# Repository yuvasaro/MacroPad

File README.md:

# MacroPad Project
UCSD HKN Project Team 2024-2025

The MacroPad project is a physical macro keyboard that interacts with a companion desktop app, allowing users to trigger customized hotkeys and launch executables across different applications. From designing the PCB and firmware to building the cross-platform desktop interface, we constructed both the hardware and software aspects of this project end-to-end.

[MacroPad Project Documentation.pdf](https://github.com/user-attachments/files/27936859/MacroPad.Project.Documentation.pdf)

## System Overview
On the physical aspect, the MacroPad is a palm-sized mechanical keyboard built around an ESP32 module, featuring 9 hot-swappable keys, 2 rotary encoders, and a small OLED screen on each key that displays context-aware icons. The board connects to a desktop app over USB, sending key and encoder events while receiving profile-switch commands in return.

The desktop app runs as a background system-tray agent on Windows and macOS, automatically detecting the active application and switching between six user-configurable profiles in real time. Each profile holds 9 macros — either keystroke combinations or executable launches — and is saved locally to the OS config directory. A QML-based GUI lets users drag-and-drop icons onto keys, configure macros, and preview what will appear on each OLED display.

## Project Structure
Unlike typical macro pads that require manual profile switching, MacroPad automatically detects the active application on your computer and switches to the matching profile in real time. 

- **Macro class:** contains information about the type and content of each key.   
- **Profile class:** contains 9 macro keys.   
   - We can set up multiple profiles. profile objects are saved to the cross-platform config directory, making the app a background agent.     
   - Similar to how Logitech G Hub keeps running after the window is closed
- **UI:** A basic UI featuring the 9 key-grid for the general profile and 6 other profiles. 
   - Each key opens a configuration page where users can assign keystroke combination or an executable path which are saved to a file.
- **Hotkey Registering:** We can enter the key type and content as parameters, so it will be registering the information into a macro key in the current profile we are on.
- **Hotkey Triggering:** Everytime a hotkey is pressed, the registered executable or keystrokes will be triggered. We worked on translates a string into a list of keys that the computer can interpret. 
## Dependencies
Mac OS  
Windows 10

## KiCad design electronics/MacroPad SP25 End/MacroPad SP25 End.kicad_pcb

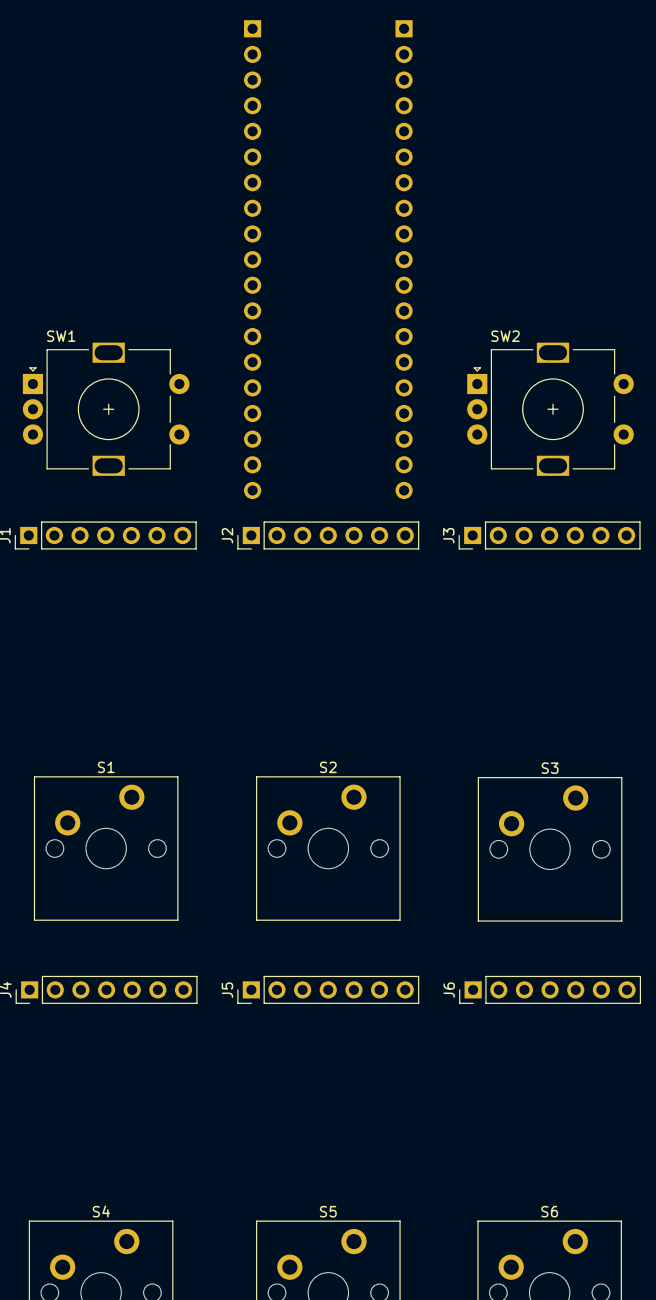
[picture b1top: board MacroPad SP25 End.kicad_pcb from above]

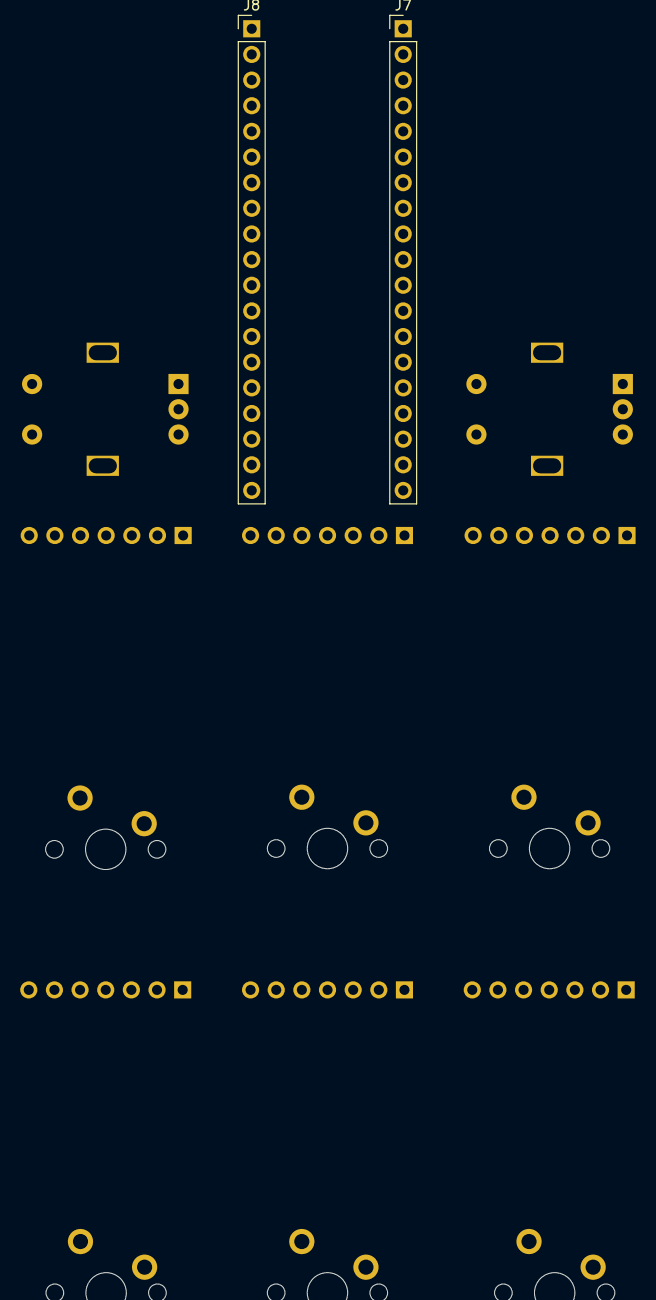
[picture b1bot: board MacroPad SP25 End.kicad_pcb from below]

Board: 2 copper layers, 16 parts (2 on the bottom side), 24 nets, no tracks yet.

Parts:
J1, J2, J3, J4, J5, J6: Conn_01x07_Pin; PinHeader_1x07_P2.54mm_Vertical
J7, J8: Conn_01x19_MountingPin; PinHeader_1x19_P2.54mm_Vertical
S1, S2, S3, S4, S5, S6: Keyswitch; MX_PCB_1.00u
SW1, SW2: RotaryEncoder_Switch; RotaryEncoder_Alps_EC11E-Switch_Vertical_H20mm

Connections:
CS1: J1.7, J8.4
CS2: J2.7, J8.10
CS3: J3.7, J7.13
CS4: J4.7, J7.12
CS5: J5.7, J7.9
CS6: J6.7, J7.8
DC: J1.6, J2.6, J3.6, J4.6, J5.6, J6.6, J8.5
Down1: J8.17, SW1.B
Down2: J8.8, SW2.B
GND: J1.1, J2.1, J3.1, J4.1, J5.1, J6.1, J8.19, S1.2, S2.2, S3.2, S4.2, S5.2, S6.2, SW1.C, SW1.S1, SW2.C, SW2.S1
Key1: J7.7, S1.1
Key2: J8.12, S2.1
Key3: J7.14, S3.1
Key4: J7.17, S4.1
Key5: J7.16, S5.1
Key6: J7.15, S6.1
Push1: J8.14, SW1.S2
Push2: J7.10, SW2.S2
RES: J1.5, J2.5, J3.5, J4.5, J5.5, J6.5, J8.7
SCL: J1.3, J2.3, J3.3, J4.3, J5.3, J6.3, J8.11
SDA: J1.4, J2.4, J3.4, J4.4, J5.4, J6.4, J8.18
Up1: J8.9, SW1.A
Up2: J7.11, SW2.A
VCC: J1.2, J2.2, J3.2, J4.2, J5.2, J6.2, J7.19

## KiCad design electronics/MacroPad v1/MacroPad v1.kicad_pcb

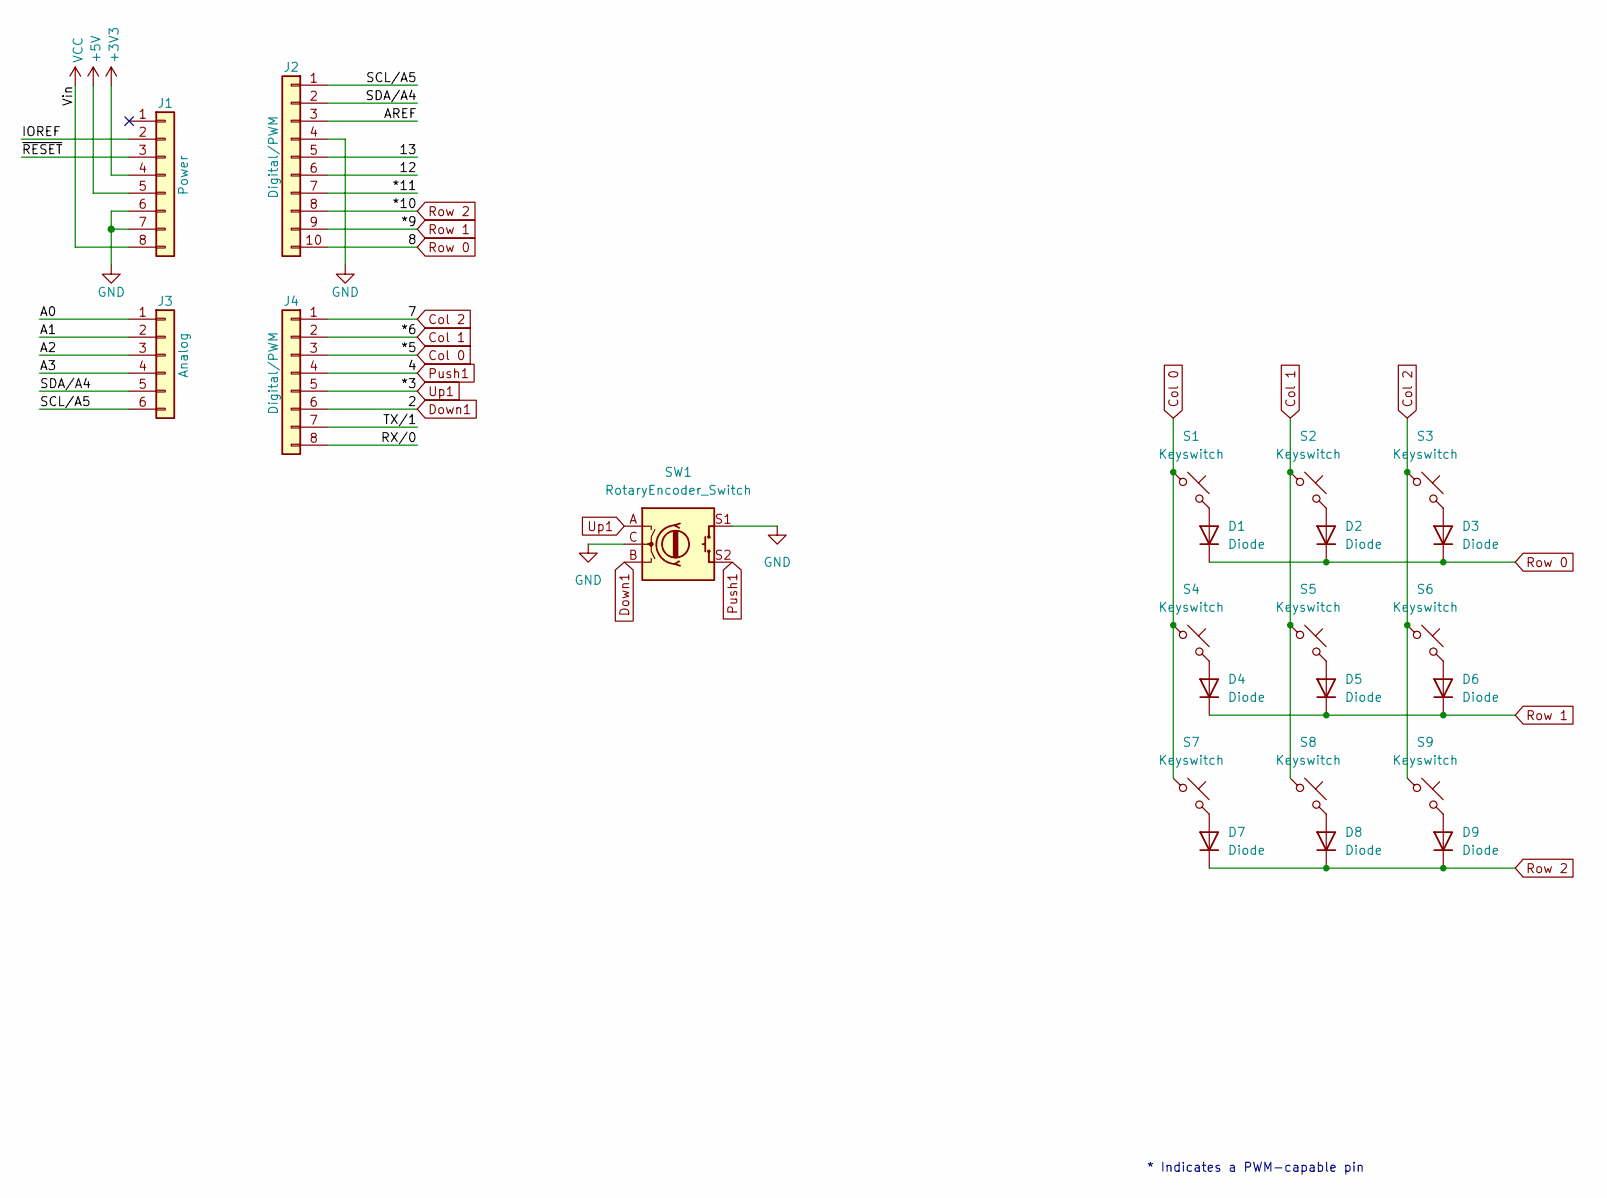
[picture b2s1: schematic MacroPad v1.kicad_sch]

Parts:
D1, D2, D3, D4, D5, D6, D7, D8, D9: Diode; Diode_DO-35
J1: Power; PinSocket_1x08_P2.54mm_Vertical
J2: Digital/PWM; PinSocket_1x10_P2.54mm_Vertical
J3: Analog; PinSocket_1x06_P2.54mm_Vertical
J4: Digital/PWM; PinSocket_1x08_P2.54mm_Vertical
S1, S2, S3, S4, S5, S6, S7, S8, S9: Keyswitch; MX_PCB_1.00u
SW1: RotaryEncoder_Switch; RotaryEncoder_Alps_EC11E-Switch_Vertical_H20mm

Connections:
+3V3: J1.4
+5V: J1.5
/12: J2.6
/13: J2.5
/*11: J2.7
/A0: J3.1
/A1: J3.2
/A2: J3.3
/A3: J3.4
/AREF: J2.3
/IOREF: J1.2
/RX/0: J4.8
/SCL/A5: J2.1, J3.6
/SDA/A4: J2.2, J3.5
/TX/1: J4.7
/~RESET: J1.3
Col 0: J4.3, S1.1, S4.1, S7.1
Col 1: J4.2, S2.1, S5.1, S8.1
Col 2: J4.1, S3.1, S6.1, S9.1
Down1: J4.6, SW1.B
GND: J1.6, J1.7, J2.4, SW1.C, SW1.S1
unnamed: D1.2 (A), S1.2
unnamed: D2.2 (A), S2.2
unnamed: D3.2 (A), S3.2
unnamed: D4.2 (A), S4.2
unnamed: D5.2 (A), S5.2
unnamed: D6.2 (A), S6.2
unnamed: D7.2 (A), S7.2
unnamed: D8.2 (A), S8.2
unnamed: D9.2 (A), S9.2
Push1: J4.4, SW1.S2
Row 0: D1.1 (K), D2.1 (K), D3.1 (K), J2.10
Row 1: D4.1 (K), D5.1 (K), D6.1 (K), J2.9
Row 2: D7.1 (K), D8.1 (K), D9.1 (K), J2.8
Up1: J4.5, SW1.A
VCC: J1.8

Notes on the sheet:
* Indicates a PWM-capable pin

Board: 2 copper layers, 27 parts (9 on the bottom side), 21 nets, no tracks yet.

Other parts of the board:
MH1, MH2, MH3, MH4: MountingHole_3.2mm

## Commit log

2025-02-08 Created software folder
2025-02-09 Added software/build to gitignore
2025-02-09 Modified CMakeLists to run application on all platforms
2025-02-10 Apps and Chat - no box
    Added program execution and keystroke functionality. Removed the initial "Ok" box, and renamed to Config Software. Also the app now minimizes on pressing "X".
2025-02-10 Test of push?
    same changes as before
2025-02-11 new release func
2025-02-12 macro and profile class
2025-02-12 restore changes
2025-02-12 fixes
2025-02-12 profile and macro before testing
2025-02-12 Removed build files, moved include shellapi to windows-only code
2025-02-12 Fixed gitignore
2025-02-13 Opening apps and running executables works on mac
2025-02-13 worked
2025-02-13 removed extra stuffs in main, makes it work in mainwindows
2025-02-13 add press
2025-02-14 testing
2025-02-14 fixed bugs; working macro and profile classes/methods
2025-02-15 latest fixes
2025-02-15 macos updates
2025-02-18 fixed hotkeyaction not working
2025-02-18 map Macro number keys to computer keys, created hotkeyCallback, get config directory path
2025-02-21 cross platform config directory for saving profiles; tested for MacOS so far
2025-02-22 latest changes (config directories)
2025-02-22 Connecting Arduino to QT App
    First Attempts at establishing Serial Comm between an Arduino and the App. Using the inital versions of code. trying to trigger Alt+Space using Button 1 on Arduino.
2025-02-22 'add'
2025-02-23 Resolve merge conflicts
2025-02-23 fixed a bit
2025-02-23 bugless code
2025-02-23 fixed both version worked
2025-02-23 Removed unused macro functions
2025-02-23 changed registerGlobalHotkey
2025-02-23 Removed callback member from macro
2025-02-23 Commented out runMacro for now, will directly use hotkey code
2025-02-27 Generalized registerGlobalHotkey
2025-02-27 Changed macro/profile/config to use QString instead of std::string, and added Profile::getMacro
2025-02-27 Fixed stuff after merging main
2025-02-28 Changed Macro, Profile, Config to QObjects
2025-02-28 changed, so far worked
2025-02-28 fix hotkeyCallback on keystrokes, added debug/testing messages
2025-02-28 serial done
2025-02-28 volume too
2025-03-01 made app a background agent
2025-03-01 week 8
2025-03-01 forced plist
2025-03-01 ui integrated
2025-03-01 Fixes to get the app running
2025-03-01 fixed both function, created 3 demos as well as macro register display, deleted unneccessary functions
2025-03-02 UI fix in configuration window
2025-03-02 UI small changes and windows code
2025-03-02 Experimenting with macos hotkeys
2025-03-06 Qmap changes and calling registerGlobalHotkey (pending debug)
2025-03-08 apptracker for MacOS
2025-03-09 using QMap for UI integration
2025-03-09 working but trying to optimize apptracker
2025-03-09 intermediate changes
2025-03-09 created app name attribute for profile
2025-03-09 Fixed misplaced bracket in mainwindow.h
2025-03-09 main not working on windows
2025-03-09 Fixed weird issue in header file that caused build errors
2025-03-09 UI updates (removed onKeyConfigured)
2025-03-25 Set app and menu bar icon for MacOS
2025-03-25 Got the UI to register hotkeys successfully
2025-03-28 Macos keystrokes still not working
2025-03-29 Corrected Cmd hex value
2025-04-09 added icon for windows
2025-04-11 currentProfile changes on app switch -- but two profile lists (need fix)
2025-04-13 weirdly worked
2025-04-13 make hotkey triggering into a separate file
2025-04-13 added exe button
2025-04-13 fixed profile manager issue
2025-04-16 fix hotkeyhandler logic
2025-04-18 profile switching in mainwindow and expose profiles to QML
2025-04-18 Temp commit to move work to correct branch
2025-04-18 set_images
2025-04-18 expose profiles list to QML
2025-04-20 apptracker working
2025-04-20 working and better apptracker
2025-04-23 added initial schem for 9 key pcb
2025-04-23 added key workshop files
2025-04-23 updated pcb for 9 key no display 1 knob
2025-04-25 working UI uses backend
2025-04-25 connected backend with frontend
2025-04-26 added a check so hotkeys don't register multiple times
2025-04-26 FINALLY fixed the saving issue -- had to remove a colon
2025-04-27 serial port
2025-04-27 added screen on side pcb
2025-04-27 final fix for saving and loading profiles
2025-04-30 in progress of fixing things
2025-04-30 at least the app is working
2025-05-01 fix application
2025-05-02 added execuatehotkey in hotkeyhandler and made it working, moved all the helper functions inside hotkeyhandler
2025-05-02 I lied, now it actually works
2025-05-02 added qdebug for mac
2025-05-02 Added currentProfile to HotkeyHandler
2025-05-04 encoder UI
2025-05-04 scrolling working
2025-05-06 working profile switching for real
2025-05-08 updated sp25 end -- wiring to esp and routing left
2025-05-09 added araav's code, added auto scroll and zoom in and out
2025-05-09 browser tab switching working
2025-05-09 reformatted and ready for mac people
2025-05-09 not much left
2025-05-11 moved knob functions into a separate file
2025-05-11 my code
2025-05-11 updated keystroke combination dropbox
2025-05-11 Updated gitignore
2025-05-11 Removed build files hopefully?
2025-05-11 Moved Apple-specific thing into ifdef
2025-05-11 Fixed some bugs hopefully
2025-05-11 Added ifdefs for windows-specific control code
2025-05-11 Fixed hotkey triggering from hardware I think
2025-05-11 Just printing the codes left
2025-05-11 Should work now
2025-05-12 new sp25 ewnd
2025-05-13 Started new PCB design 2x3
2025-05-14 long added
2025-05-14 SerialHandler fixed -- key detected but macro not triggered
2025-05-14 added INO for 6 display 6 key 2 knob
2025-05-15 did nothing
2025-05-15 profile switching working on windows now, keyboard testing behavior aligns with minipad key triggering.
2025-05-16 app names are displayed for all profiles on load
2025-05-18 added volume control back, working on executeEncoder
2025-05-18 app not crashing
2025-05-18 Integrated mac volume from MacroKeyWorkshop
2025-05-18 fixed profile sending
2025-05-19 Mac volume, app switching, zoom in/out all working
2025-05-19 Fixed minor bug
2025-05-22 successfully register profile, executeEncoder function working
2025-05-23 Create qtserialport
2025-05-23 adde brightness
2025-05-23 app volume
2025-05-23 app icons for ui
2025-05-25 trying to fix knob register
2025-05-25 brightness for now
2025-05-28 stuffs
2025-05-30 fixed loadprofile, also twisted encoder selection behavior, still not loading correctly
2025-05-30 check
2025-05-30 working scrolling for mac
2025-06-01 general profile saving working
2025-06-01 fix if def
2025-10-06 Fixed knobhandler errors on mac
2025-10-06 Formatting changes
2025-10-06 Removed fileio.h/fileio.cpp
2025-10-12 Fixed debug map error
2025-10-12 Execute encoder working for mac
2025-10-20 fixed knob handler not updating issue
2025-10-20 tab switching chrome for mac
2025-10-26 refresh signal implemented
2025-10-26 Loop done Transfer left
2025-11-01 Added all INOs to repo
2025-11-02 added window swapping check before open up a new executable window
2025-11-02 little
2025-11-02 Use executeEncoder for knob 2
2025-11-02 Replaced keystroke image
2025-11-09 Updated keystroke icon
2025-11-09 fix image extraction issue and fixed certain key not mapped
2025-11-09 fixed bunch of annoying output messages when shutting down
2025-11-09 initial attempt for chrome switching
2025-11-09 osascript solution for chrome swtiching. works
2025-11-09 profile icon implemented
2025-11-09 Key Config window UI updates
2025-11-09 Icon refresh on restart
2025-11-09 iOS Applications Icon Path Updated
2025-11-23 smal chnage but algo pretty much works
2025-11-23 driver start added
2025-11-23 icon update fix
2026-02-07 added keystrokerecorder
2026-02-07 keystroke recording tested
2026-02-24 windows implementation, recording tested in mainwindows.cpp, added maps to both OS
2026-02-24 more fix
2026-02-28 Add keystroke recorder UI with label support
2026-05-17 Update README with project documentation link
    Added link to project documentation in README.
2026-05-17 Enhance README with detailed project description
    Expanded project description and system overview in README.
2026-05-17 Add brief project description to README
2026-05-22 Fix macOS build and macro controls
2026-05-23 Support plain serial key commands
2026-05-23 Fix macOS Qt controls rendering
2026-05-24 fixed build errors
2026-05-24 edited read me + UI fix
2026-05-24 edited to use the new icon
2026-05-24 icon fix
2026-05-24 Fix macOS bundle icon path
2026-05-24 Use new macOS app icon
